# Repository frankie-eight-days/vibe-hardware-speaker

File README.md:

# Vibe hardware: a portable stereo Bluetooth speaker designed with LLM agents

A JBL Flip/Charge-class portable speaker, designed end to end with Claude Code agents and one human making the calls: requirements, part selection, circuit specs, KiCad schematic, simulations (acoustic BEM/FEM, SPICE, PDN), mechanical packaging and, next, PCB layout. The full story, including what went wrong, is in the write-up: [`docs/build/design_doc.pdf`](docs/build/design_doc.pdf). An interactive page explaining every simulation is in [`docs/viz/`](docs/viz/) (open `index.html`).

## The speaker

- **Stereo 2-way, bi-amped:** 2× Dayton ND65-8 woofers, 2× Peerless OT19NC00-04 tweeters (angled up 40°), 2× Dayton DMA58-PR passive radiators on the end caps. Bass to ~64 Hz (−3 dB), ~90 dB pink noise at 1 m on a desk.
- **Electronics:** ESP32-WROVER-E (Bluetooth A2DP + Wi-Fi EQ web UI), 2× TI TAS5805M class-D amps with DSP crossover/EQ/limiters, 18 V TPS61178 boost, BQ25792 buck-boost charger with USB-C PD (CH224Q), 2S Li-ion pack with on-board protection and balancing.
- **UI:** 1.28" round display, encoder, MEMS mic for placement-aware auto-EQ, power button.
- **Mechanics:** Ø95 × 210 mm capsule, five FDM-printed PETG parts, ~0.85 L net volume, ~12.8 h at moderate volume.
- **Manufacturing:** 4-layer main board assembled by JLCPCB from LCSC parts.

| | |
|---|---|
|  |  |
|  |  |

*Renders are placeholders until the Blender pass (after PCB layout and detailed CAD).*

## Status

| Stage | State |
|---|---|
| Requirements, research, part selection | Done |
| Circuit specs (power, signal, UI board) | v1.3 / v1.2 |
| Schematic | **v0.2**, release review passed with no blockers (`docs/review/`) |
| Simulations: acoustics, SPICE, PDN | Done (pre-layout) |
| Mechanical concept | Done (`mech/concept/`) |
| PCB layout | In progress |
| Thermal, post-layout PDN, EM hot-loop sims | After layout |
| Blender renders, build, REW measurements, firmware | Planned |

## Repository layout

| Path | Contents |
|---|---|
| `docs/requirements.md` | Single source of truth for product decisions |
| `docs/spec_*.md` | Pin-exact circuit specifications |
| `docs/eco_*.md`, `docs/review/` | Engineering changes and release reviews |
| `docs/process_log.md` | How the agents were orchestrated, and what went wrong |
| `docs/layout_principles.md` | Layout rules the PCB must meet |
| `docs/writeup/`, `docs/build/` | LaTeX write-up and its PDF |
| `docs/figures/` | All simulation figures (PDF + PNG) |
| `docs/renders/` | Blender renders (placeholders for now) |
| `research/` | Parts, drivers, firmware/tool research |
| `hw/mainboard/` | KiCad project; `hw/releases/` frozen snapshots; `hw/lib/` custom symbols/footprints |
| `mech/concept/` | Scripted FreeCAD packaging model, STEP, board envelopes |
| `sim/` | Acoustic, SPICE and PDN simulations (`run_all.sh` in each) |
| `kb/datasheets/` | Datasheet layout notes with page citations (vendor PDFs not included) |
| `tools/` | Helpers, e.g. the TAS5805M biquad encoder |

## Reproducing the simulations

```sh
python3 -m venv .venv && .venv/bin/pip install -r requirements-sim.txt
sim/acoustics/run_all.sh    # BEM runs take ~1 h on a laptop CPU
sim/spice/run_all.sh        # needs ngspice (brew install ngspice)
```

3D/CAD files and large simulation outputs (`*.step`, `*.stl`, `*.FCStd`, `*.npz`, raw waveforms) are stored with Git LFS: install it (`brew install git-lfs && git lfs install`) before cloning, or run `git lfs pull` afterwards.

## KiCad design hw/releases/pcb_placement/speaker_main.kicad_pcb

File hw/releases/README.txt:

v1 schematic snapshot, 2026-11-24, before the readability redraw.
ERC 0 violations. Exports in mainboard_v1/out/. Libraries frozen in releases/lib/.

v0.2 (release-ready for placement), 2026-11-24: redrawn, ECO-001 + ECO-002 applied, release review: no blockers, conditional on open should-fix items (docs/review/release_review.md, release_review_v0.2.md). Libraries frozen in releases/lib_v0.2/.

v0.3, 2026-11-25: ECO-004 (C605 47 uF Al-elec ESR-damped VBUS bulk, docs/eco_004.md). ERC 0 violations; netlist vs v0.2 differs only by C605 on VBUS/GND. Schematic-only snapshot (no .kicad_pcb: layout is live). Libraries: releases/lib_v0.2/.

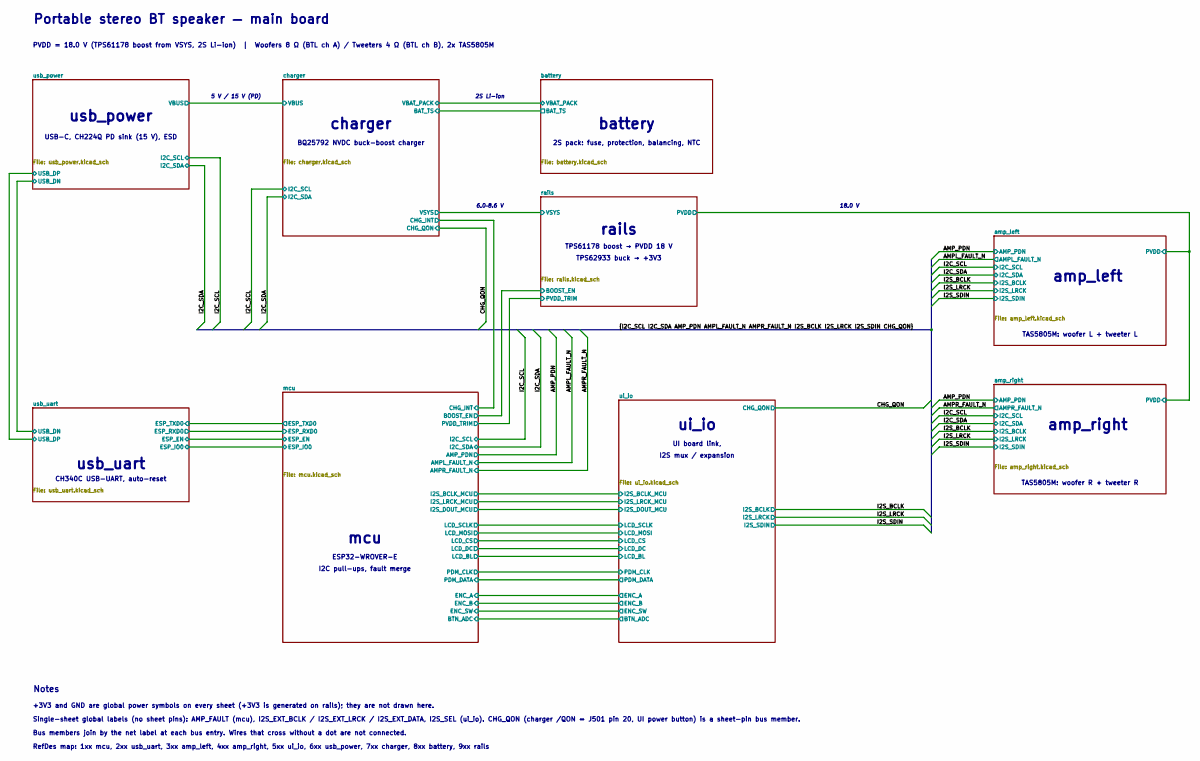
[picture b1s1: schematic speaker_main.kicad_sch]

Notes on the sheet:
Portable stereo BT speaker — main board
PVDD = 18.0 V (TPS61178 boost from VSYS, 2S Li-ion) | Woofers 8 Ω (BTL ch A) / Tweeters 4 Ω (BTL ch B), 2x TAS5805M
usb_power
USB-C, CH224Q PD sink (15 V), ESD
charger
BQ25792 NVDC buck-boost charger
battery
2S pack: fuse, protection, balancing, NTC
rails
TPS61178 boost → PVDD 18 V
TPS62933 buck → +3V3
usb_uart
CH340C USB-UART, auto-reset
mcu
ESP32-WROVER-E
I2C pull-ups, fault merge
ui_io
UI board link,
I2S mux / expansion
amp_left
TAS5805M: woofer L + tweeter L
amp_right
TAS5805M: woofer R + tweeter R
5 V / 15 V (PD)
2S Li-ion
6.0–8.6 V
18.0 V
Notes
+3V3 and GND are global power symbols on every sheet (+3V3 is generated on rails); they are not drawn here.
Bus members join by the net label at each bus entry. Wires that cross without a dot are not connected.
RefDes map: 1xx mcu, 2xx usb_uart, 3xx amp_left, 4xx amp_right, 5xx ui_io, 6xx usb_power, 7xx charger, 8xx battery, 9xx rails
Single-sheet global labels (no sheet pins): AMP_FAULT (mcu), I2S_EXT_BCLK / I2S_EXT_LRCK / I2S_EXT_DATA, I2S_SEL (ui_io). CHG_QON (charger /QON ↔ J501 pin 20, UI power button) is a sheet-pin bus member.

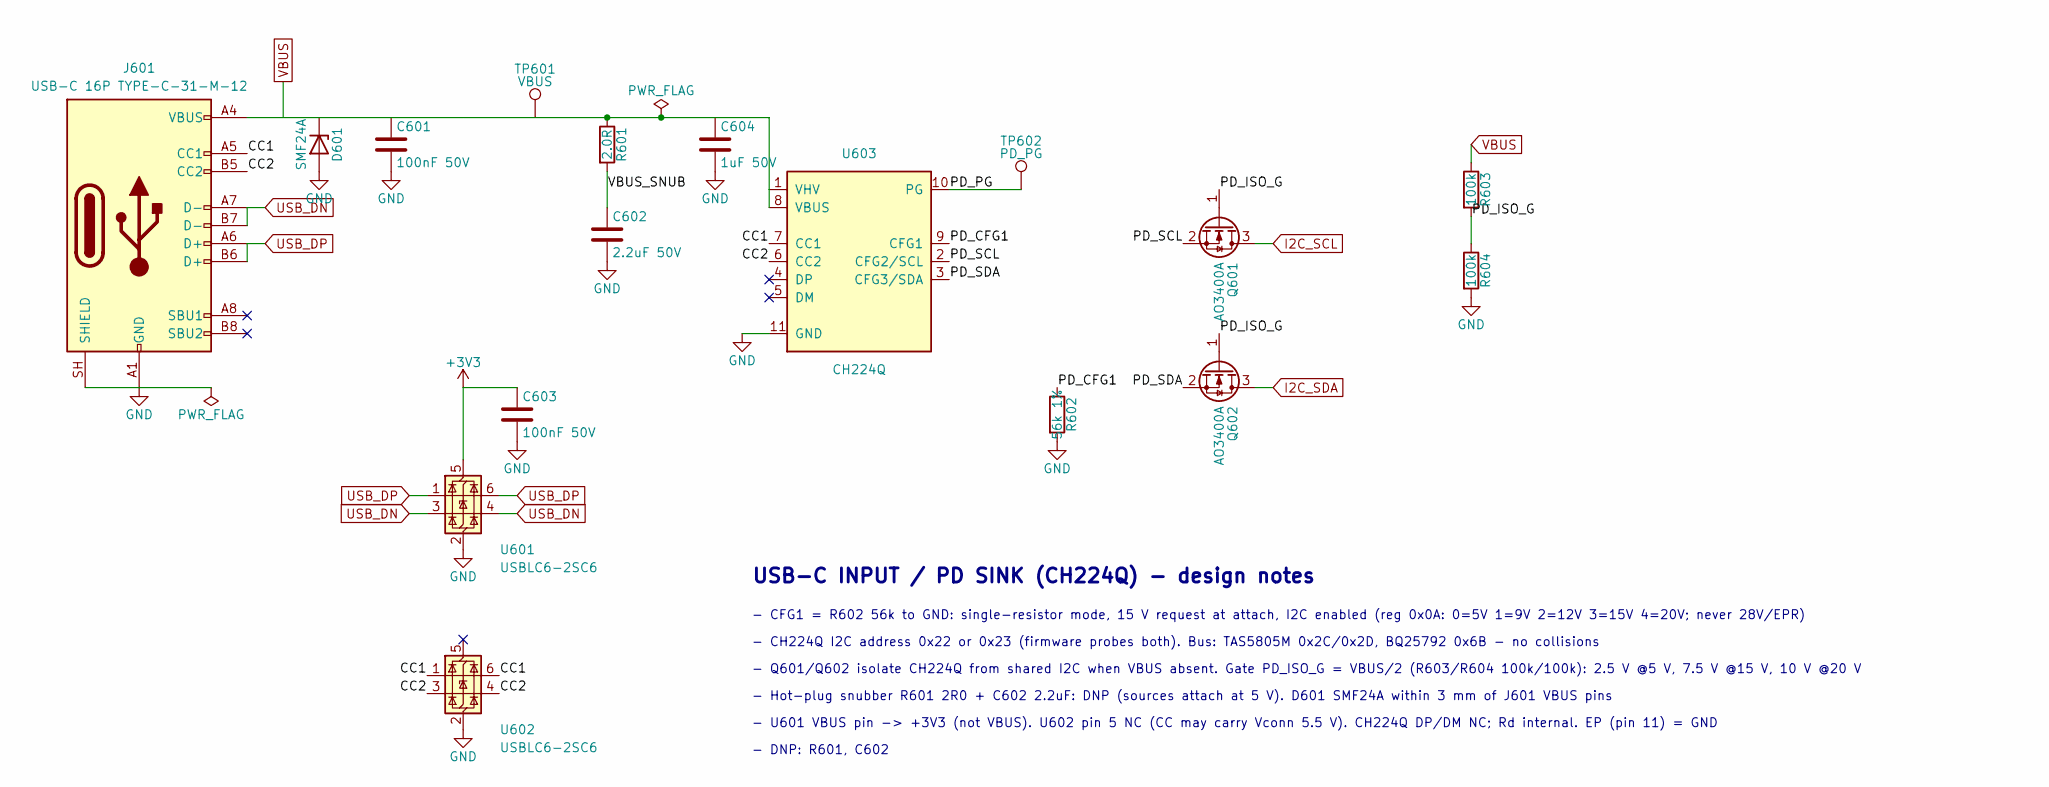
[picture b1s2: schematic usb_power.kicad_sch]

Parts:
C601, C603: 100nF 50V; C_0603_1608Metric; LCSC C14663
C602: 2.2uF 50V; C_0805_2012Metric; LCSC C377773
C604: 1uF 50V; C_0603_1608Metric; LCSC C15849
D601: SMF24A; D_SOD-123F; LCSC C123810
J601: USB-C 16P TYPE-C-31-M-12; USB_C_Receptacle_HRO_TYPE-C-31-M-12; LCSC C165948
Q601, Q602: AO3400A; SOT-23; LCSC C20917
R601: 2.0R; R_0805_2012Metric; LCSC C2930265
R602: 56k 1%; R_0603_1608Metric; LCSC C23206
R603, R604: 100k; R_0603_1608Metric; LCSC C25803
TP601: VBUS; TestPoint_Pad_D1.5mm
TP602: PD_PG; TestPoint_Pad_D1.5mm
U601, U602: USBLC6-2SC6; SOT-23-6; LCSC C2687116
U603: CH224Q; Texas_DSQ0010A_WSON-10-1EP_2x2mm_P0.4mm_EP0.9x1.5mm; LCSC C46061833

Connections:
+3V3: C603.1, U601.5 (VBUS); also elsewhere on the board
/I2C_SCL: Q601.3 (D); also elsewhere on the board
/I2C_SDA: Q602.3 (D); also elsewhere on the board
/usb_power/CC1: J601.A5 (CC1), U602.1 (I/O1), U602.6 (I/O1), U603.7 (CC1)
/usb_power/CC2: J601.B5 (CC2), U602.3 (I/O2), U602.4 (I/O2), U603.6 (CC2)
/usb_power/PD_CFG1: R602.1, U603.9 (CFG1)
/usb_power/PD_ISO_G: Q601.1 (G), Q602.1 (G), R603.2, R604.1
/usb_power/PD_PG: TP602.1 (1_1), U603.10 (PG)
/usb_power/PD_SCL: Q601.2 (S), U603.2 (CFG2/SCL)
/usb_power/PD_SDA: Q602.2 (S), U603.3 (CFG3/SDA)
/usb_power/USB_DN: J601.A7 (D-), J601.B7 (D-), U601.3 (I/O2), U601.4 (I/O2); also elsewhere on the board
/usb_power/USB_DP: J601.A6 (D+), J601.B6 (D+), U601.1 (I/O1), U601.6 (I/O1); also elsewhere on the board
/usb_power/VBUS_SNUB: C602.1, R601.2

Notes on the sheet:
USB-C INPUT / PD SINK (CH224Q) - design notes
- CFG1 = R602 56k to GND: single-resistor mode, 15 V request at attach, I2C enabled (reg 0x0A: 0=5V 1=9V 2=12V 3=15V 4=20V; never 28V/EPR)
- CH224Q I2C address 0x22 or 0x23 (firmware probes both). Bus: TAS5805M 0x2C/0x2D, BQ25792 0x6B - no collisions
- Q601/Q602 isolate CH224Q from shared I2C when VBUS absent. Gate PD_ISO_G = VBUS/2 (R603/R604 100k/100k): 2.5 V @5 V, 7.5 V @15 V, 10 V @20 V
- Hot-plug snubber R601 2R0 + C602 2.2uF: DNP (sources attach at 5 V). D601 SMF24A within 3 mm of J601 VBUS pins
- U601 VBUS pin -> +3V3 (not VBUS). U602 pin 5 NC (CC may carry Vconn 5.5 V). CH224Q DP/DM NC; Rd internal. EP (pin 11) = GND
- DNP: R601, C602

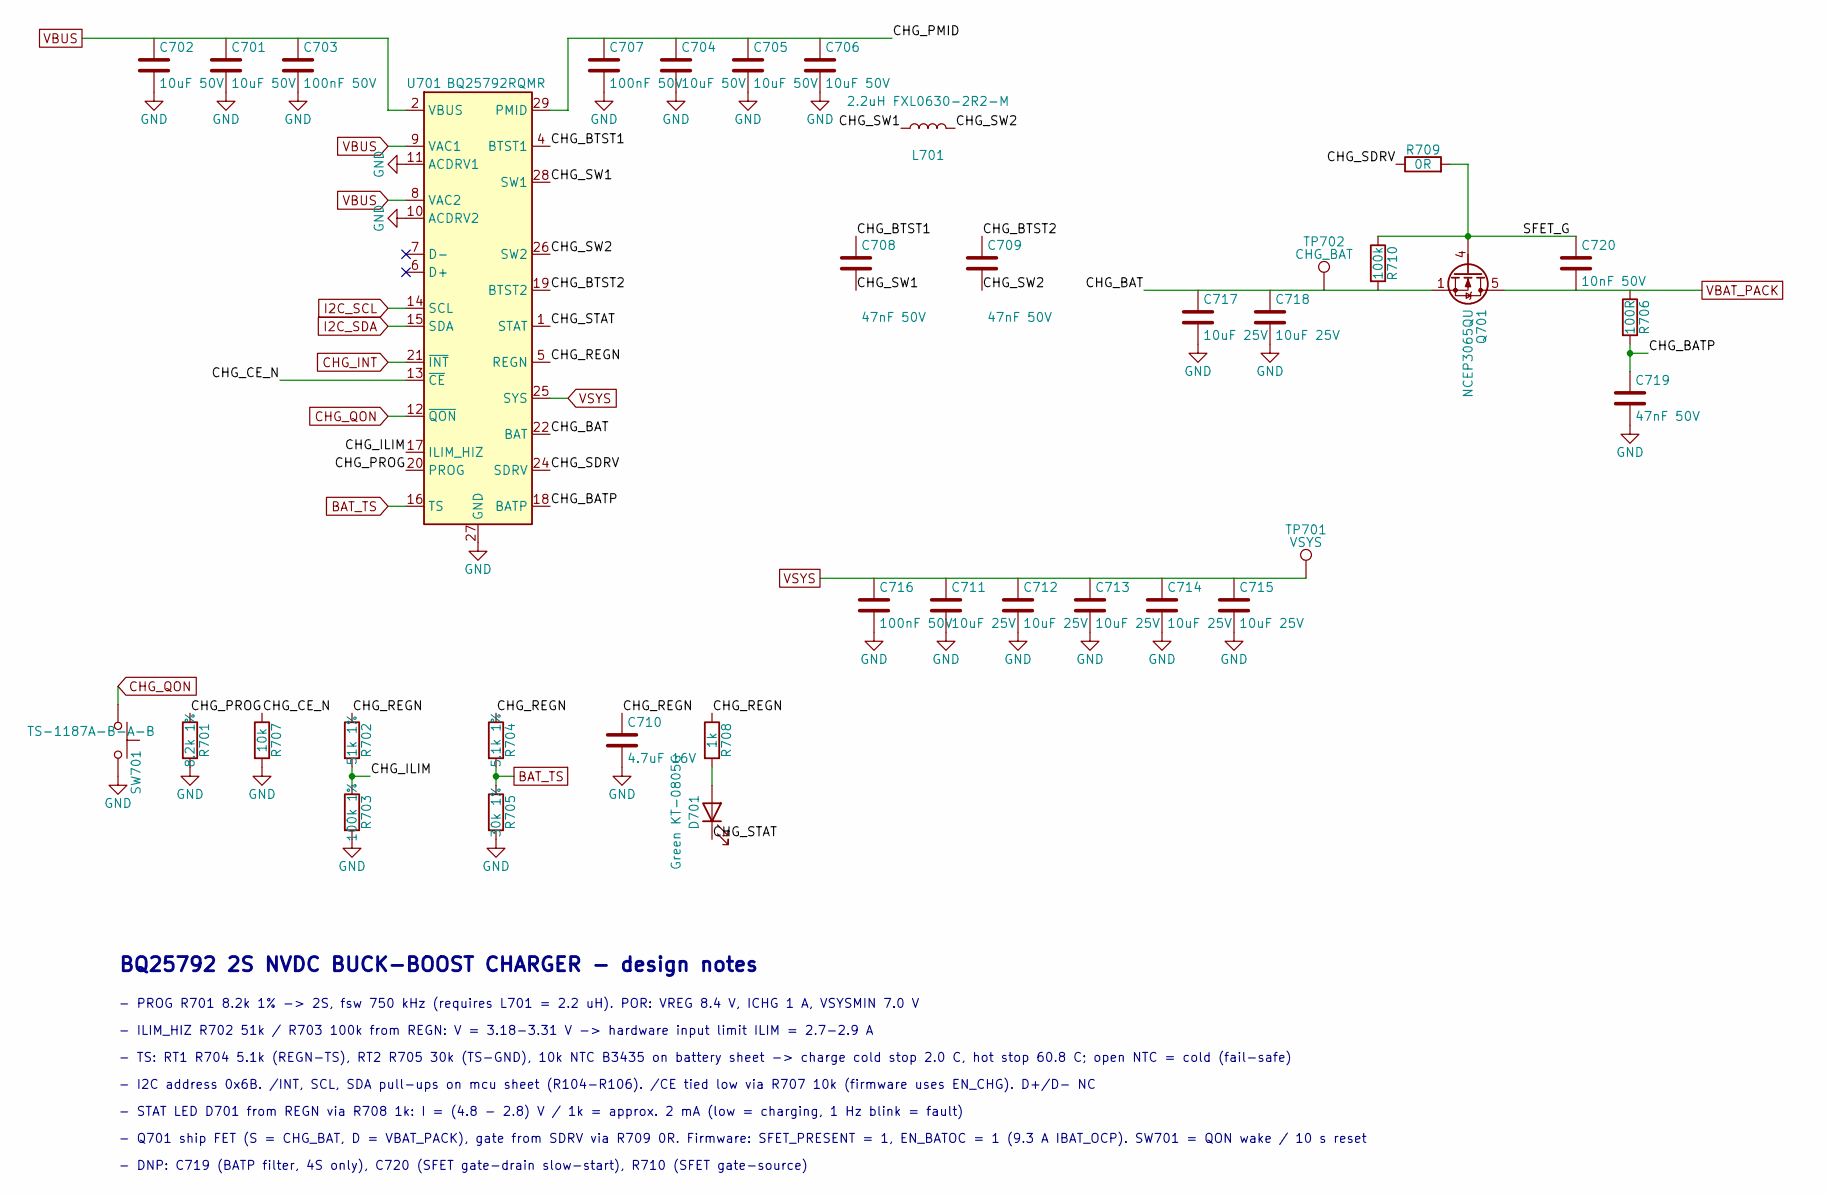
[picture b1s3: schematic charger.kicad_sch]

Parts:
C701, C702, C704, C705, C706: 10uF 50V; C_1206_3216Metric; LCSC C13585
C703, C707, C716: 100nF 50V; C_0603_1608Metric; LCSC C14663
C708, C709, C719: 47nF 50V; C_0603_1608Metric; LCSC C1622
C710: 4.7uF 16V; C_0603_1608Metric; LCSC C19666
C711, C712, C713, C714, C715, C717, C718: 10uF 25V; C_0805_2012Metric; LCSC C15850
C720: 10nF 50V; C_0603_1608Metric; LCSC C57112
D701: Green KT-0805G; LED_0805_2012Metric; LCSC C2297
L701: 2.2uH FXL0630-2R2-M; L_Changjiang_FXL0630; LCSC C167218
Q701: NCEP3065QU; VSON-8_3.3x3.3mm_P0.65mm_NexFET; LCSC C502964
R701: 8.2k 1%; R_0603_1608Metric; LCSC C25981
R702: 51k 1%; R_0603_1608Metric; LCSC C23196
R703: 100k 1%; R_0603_1608Metric; LCSC C25803
R704: 5.1k 1%; R_0603_1608Metric; LCSC C23186
R705: 30k 1%; R_0603_1608Metric; LCSC C22984
R706: 100R; R_0603_1608Metric; LCSC C22775
R707: 10k; R_0603_1608Metric; LCSC C25804
R708: 1k; R_0603_1608Metric; LCSC C21190
R709: 0R; R_0603_1608Metric; LCSC C21189
R710: 100k; R_0603_1608Metric; LCSC C25803
SW701: TS-1187A-B-A-B; SW_Push_1P1T_XKB_TS-1187A; LCSC C318884
TP701: VSYS; TestPoint_Pad_D1.5mm
TP702: CHG_BAT; TestPoint_Pad_D1.5mm
U701: BQ25792RQMR; Texas_RQM0029A_VQFN-29_4x4mm_P0.4mm; LCSC C2862876

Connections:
/CHG_QON: SW701.1, U701.12 (~QON); also elsewhere on the board
/I2C_SCL: U701.14 (SCL); also elsewhere on the board
/I2C_SDA: U701.15 (SDA); also elsewhere on the board
/battery/BAT_TS: R704.2, R705.1, U701.16 (TS); also elsewhere on the board
/battery/VBAT_PACK: C720.2, Q701.5 (D), R706.1; also elsewhere on the board
/charger/CHG_BAT: C717.1, C718.1, Q701.1 (S), Q701.2 (S), Q701.3 (S), R710.2, TP702.1 (1_1), U701.22 (BAT), U701.23 (BAT); also elsewhere on the board
/charger/CHG_BATP: C719.1, R706.2, U701.18 (BATP)
/charger/CHG_BTST1: C708.1, U701.4 (BTST1)
/charger/CHG_BTST2: C709.1, U701.19 (BTST2)
/charger/CHG_CE_N: R707.1, U701.13 (~CE)
/charger/CHG_ILIM: R702.2, R703.1, U701.17 (ILIM_HIZ)
/charger/CHG_INT: U701.21 (~INT); also elsewhere on the board
/charger/CHG_PMID: C704.1, C705.1, C706.1, C707.1, U701.29 (PMID)
/charger/CHG_PROG: R701.1, U701.20 (PROG)
/charger/CHG_REGN: C710.1, R702.1, R704.1, R708.1, U701.5 (REGN)
/charger/CHG_SDRV: R709.1, U701.24 (SDRV)
/charger/CHG_STAT: D701.1 (K), U701.1 (STAT)
/charger/CHG_SW1: C708.2, L701.1, U701.28 (SW1)
/charger/CHG_SW2: C709.2, L701.2, U701.26 (SW2)
/charger/SFET_G: C720.1, Q701.4 (G), R709.2, R710.1; also elsewhere on the board
/charger/VSYS: C711.1, C712.1, C713.1, C714.1, C715.1, C716.1, TP701.1 (1_1), U701.25 (SYS); also elsewhere on the board
unnamed: D701.2 (A), R708.2

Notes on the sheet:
BQ25792 2S NVDC BUCK-BOOST CHARGER - design notes
- PROG R701 8.2k 1% -> 2S, fsw 750 kHz (requires L701 = 2.2 uH). POR: VREG 8.4 V, ICHG 1 A, VSYSMIN 7.0 V
- ILIM_HIZ R702 51k / R703 100k from REGN: V = 3.18-3.31 V -> hardware input limit ILIM = 2.7-2.9 A
- TS: RT1 R704 5.1k (REGN-TS), RT2 R705 30k (TS-GND), 10k NTC B3435 on battery sheet -> charge cold stop 2.0 C, hot stop 60.8 C; open NTC = cold (fail-safe)
- I2C address 0x6B. /INT, SCL, SDA pull-ups on mcu sheet (R104-R106). /CE tied low via R707 10k (firmware uses EN_CHG). D+/D- NC
- STAT LED D701 from REGN via R708 1k: I = (4.8 - 2.8) V / 1k = approx. 2 mA (low = charging, 1 Hz blink = fault)
- Q701 ship FET (S = CHG_BAT, D = VBAT_PACK), gate from SDRV via R709 0R. Firmware: SFET_PRESENT = 1, EN_BATOC = 1 (9.3 A IBAT_OCP). SW701 = QON wake / 10 s reset
- DNP: C719 (BATP filter, 4S only), C720 (SFET gate-drain slow-start), R710 (SFET gate-source)

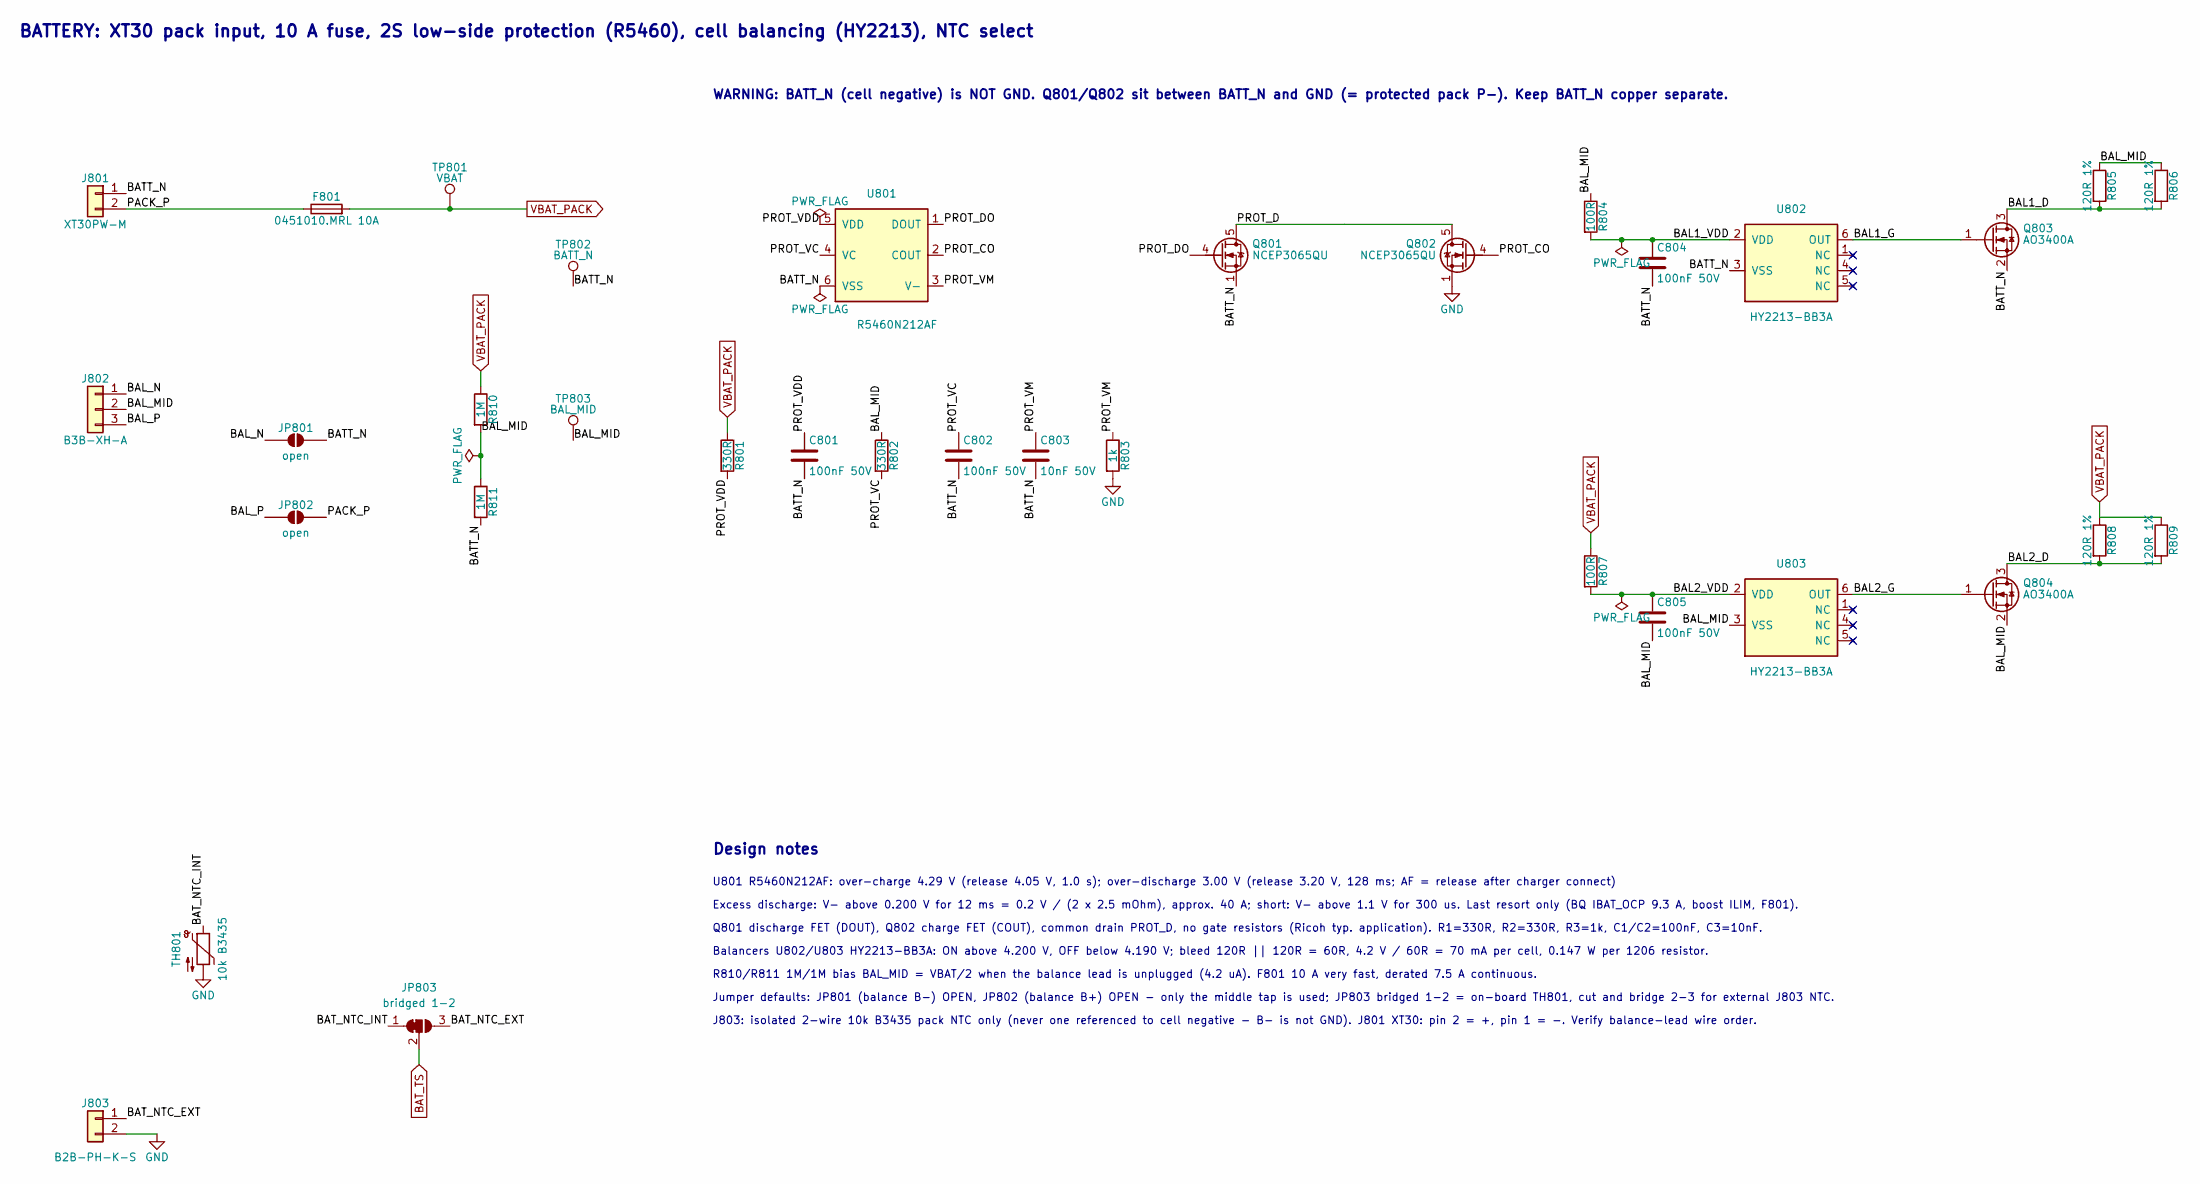
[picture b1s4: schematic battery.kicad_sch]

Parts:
C801, C802, C804, C805: 100nF 50V; C_0603_1608Metric; LCSC C14663
C803: 10nF 50V; C_0603_1608Metric; LCSC C57112
F801: 0451010.MRL 10A; Fuse_2410_6125Metric; LCSC C44479
J801: XT30PW-M; AMASS_XT30PW-M_1x02_P2.50mm_Horizontal; LCSC C431092
J802: B3B-XH-A; JST_XH_B3B-XH-A_1x03_P2.50mm_Vertical; LCSC C144394
J803: B2B-PH-K-S; JST_PH_B2B-PH-K_1x02_P2.00mm_Vertical; LCSC C131337
JP801, JP802: open; SolderJumper-2_P1.3mm_Open_RoundedPad1.0x1.5mm
JP803: bridged 1-2; SolderJumper-3_P1.3mm_Bridged12_RoundedPad1.0x1.5mm
Q801, Q802: NCEP3065QU; VSON-8_3.3x3.3mm_P0.65mm_NexFET; LCSC C502964
Q803, Q804: AO3400A; SOT-23; LCSC C20917
R801, R802: 330R; R_0603_1608Metric; LCSC C23138
R803: 1k; R_0603_1608Metric; LCSC C21190
R804, R807: 100R; R_0603_1608Metric; LCSC C22775
R805, R806, R808, R809: 120R 1%; R_1206_3216Metric; LCSC C17909
R810, R811: 1M; R_0603_1608Metric; LCSC C22935
TH801: 10k B3435; R_0603_1608Metric; LCSC C2889048
TP801: VBAT; TestPoint_Pad_D1.5mm
TP802: BATT_N; TestPoint_Pad_D1.5mm
TP803: BAL_MID; TestPoint_Pad_D1.5mm
U801: R5460N212AF; SOT-23-6; LCSC C259717
U802, U803: HY2213-BB3A; SOT-23-6; LCSC C113632

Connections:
/battery/BAL1_D: Q803.3 (D), R805.2, R806.2
/battery/BAL1_G: Q803.1 (G), U802.6 (OUT)
/battery/BAL2_D: Q804.3 (D), R808.2, R809.2
/battery/BAL2_G: Q804.1 (G), U803.6 (OUT)
/battery/BAL_N: J802.1, JP801.1 (A)
/battery/BAL_P: J802.3, JP802.1 (A)
/battery/BAT_TS: JP803.2 (C); also elsewhere on the board
/battery/PACK_P: F801.1, J801.2, JP802.2 (B)
/battery/PROT_CO: Q802.4 (G), U801.2 (COUT)
/battery/PROT_D: Q801.5 (D), Q802.5 (D)
/battery/PROT_DO: Q801.4 (G), U801.1 (DOUT)
/battery/PROT_VC: C802.1, R802.2, U801.4 (VC)
/battery/PROT_VM: C803.1, R803.1, U801.3 (V-)
/battery/VBAT_PACK: F801.2, R801.1, R807.1, R808.1, R809.1, R810.1, TP801.1 (1_1); also elsewhere on the board

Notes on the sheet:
BATTERY: XT30 pack input, 10 A fuse, 2S low-side protection (R5460), cell balancing (HY2213), NTC select
WARNING: BATT_N (cell negative) is NOT GND. Q801/Q802 sit between BATT_N and GND (= protected pack P-). Keep BATT_N copper separate.
Design notes
U801 R5460N212AF: over-charge 4.29 V (release 4.05 V, 1.0 s); over-discharge 3.00 V (release 3.20 V, 128 ms; AF = release after charger connect)
Q801 discharge FET (DOUT), Q802 charge FET (COUT), common drain PROT_D, no gate resistors (Ricoh typ. application). R1=330R, R2=330R, R3=1k, C1/C2=100nF, C3=10nF.
R810/R811 1M/1M bias BAL_MID = VBAT/2 when the balance lead is unplugged (4.2 uA). F801 10 A very fast, derated 7.5 A continuous.
Jumper defaults: JP801 (balance B-) OPEN, JP802 (balance B+) OPEN - only the middle tap is used; JP803 bridged 1-2 = on-board TH801, cut and bridge 2-3 for external J803 NTC.
J803: isolated 2-wire 10k B3435 pack NTC only (never one referenced to cell negative - B- is not GND). J801 XT30: pin 2 = +, pin 1 = -. Verify balance-lead wire order.
Excess discharge: V- above 0.200 V for 12 ms = 0.2 V / (2 x 2.5 mOhm), approx. 40 A; short: V- above 1.1 V for 300 us. Last resort only (BQ IBAT_OCP 9.3 A, boost ILIM, F801).
Balancers U802/U803 HY2213-BB3A: ON above 4.200 V, OFF below 4.190 V; bleed 120R || 120R = 60R, 4.2 V / 60R = 70 mA per cell, 0.147 W per 1206 resistor.

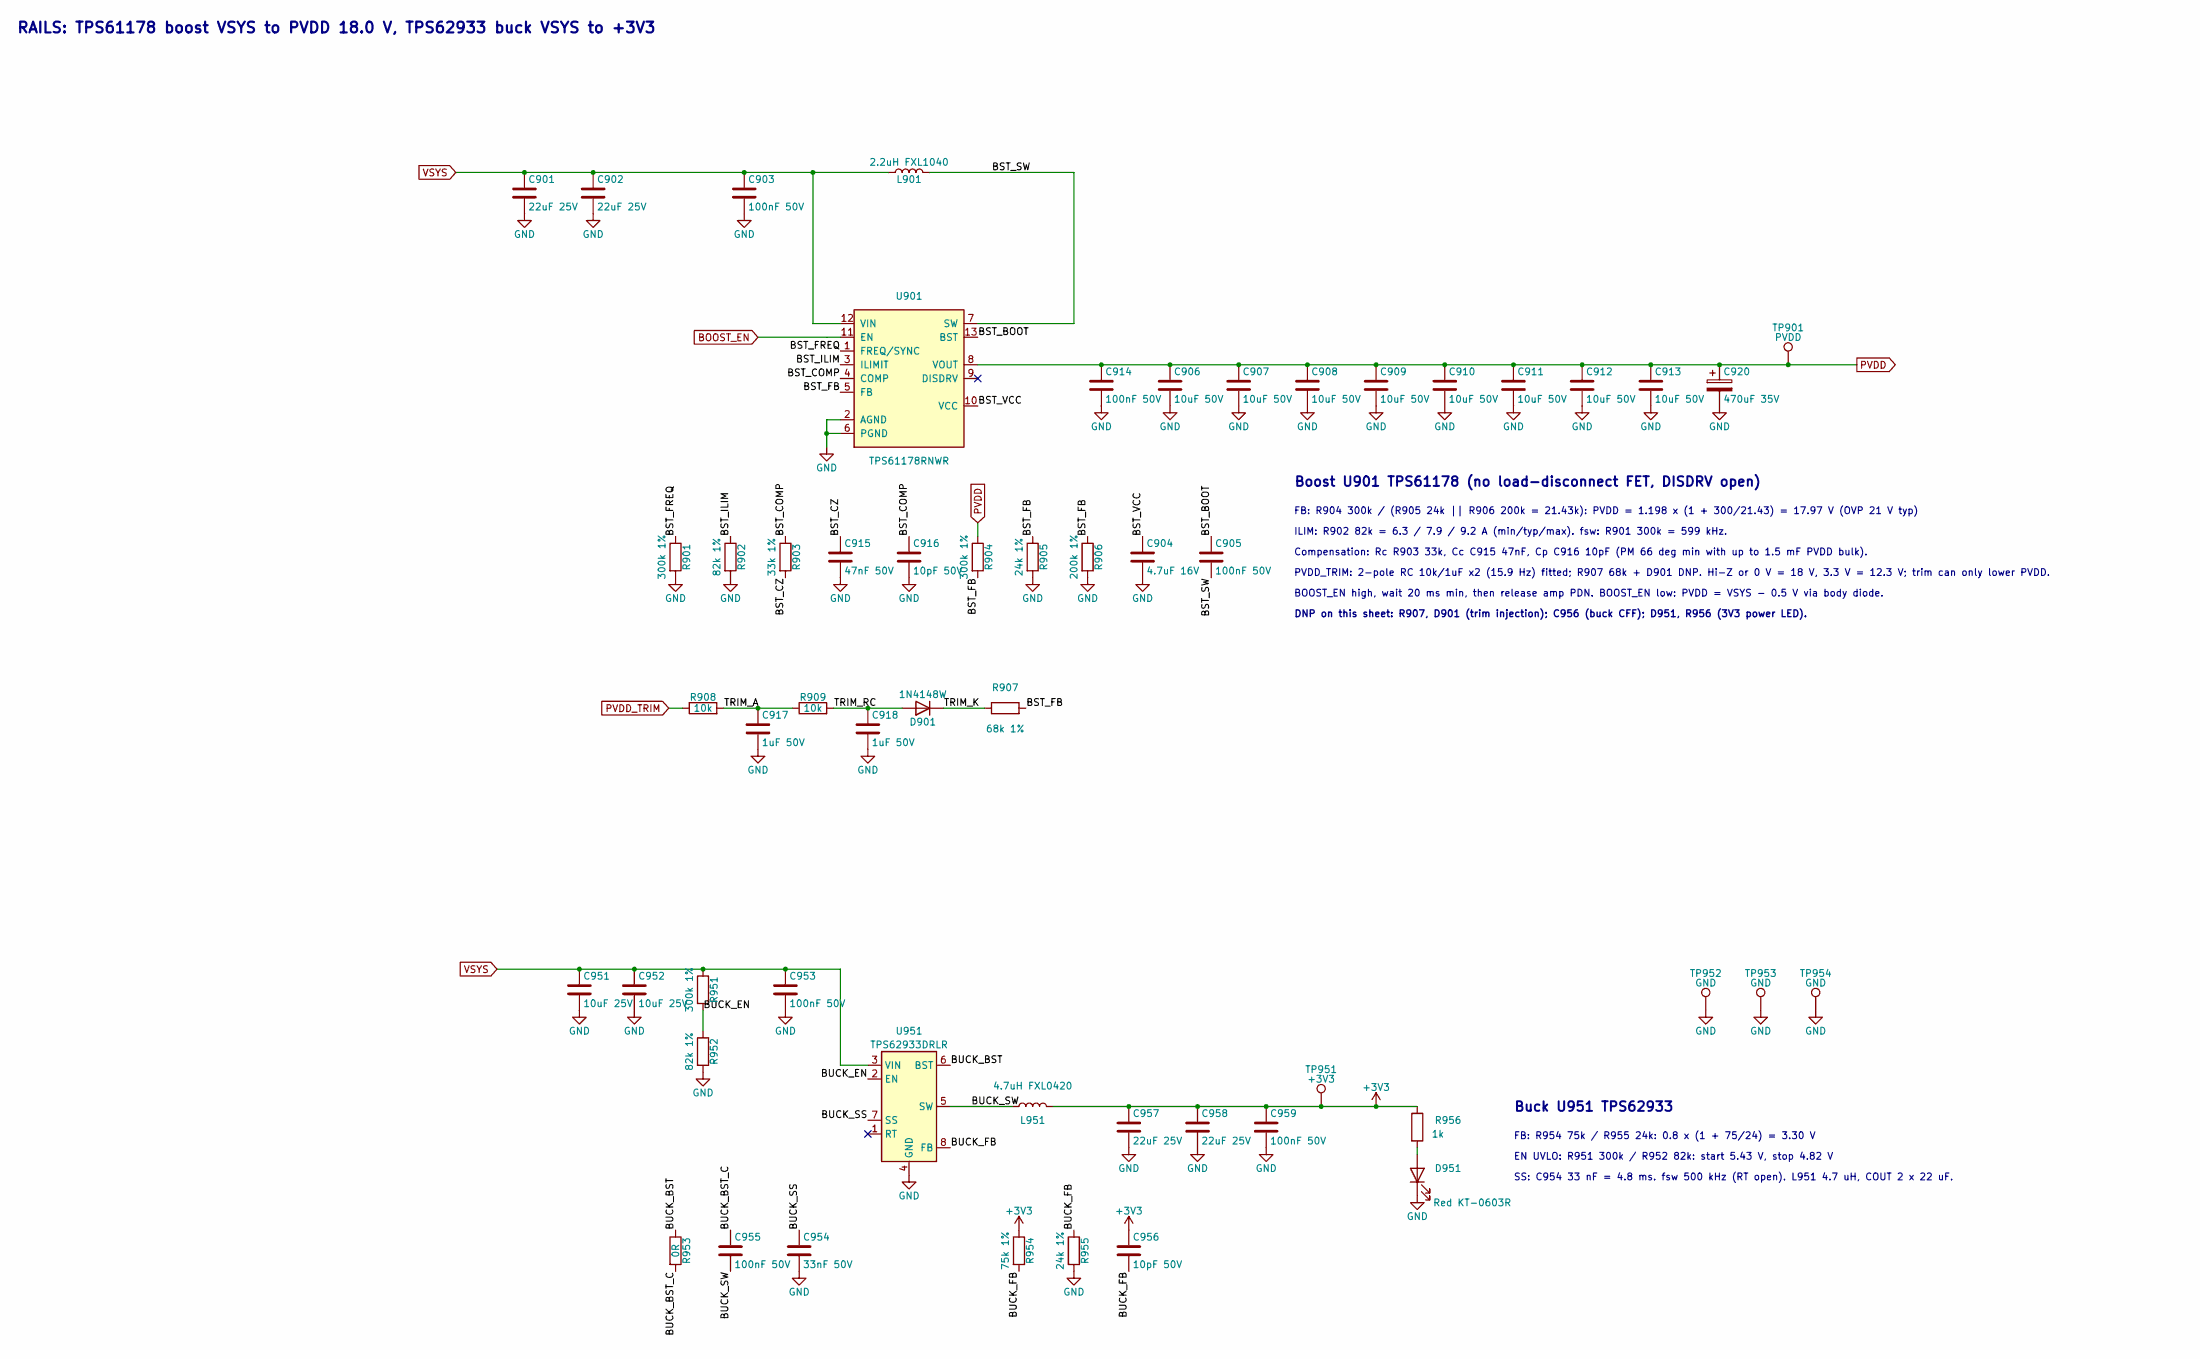
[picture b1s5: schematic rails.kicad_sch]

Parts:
C901, C902, C957, C958: 22uF 25V; C_1206_3216Metric; LCSC C12891
C903, C905, C914, C953, C955, C959: 100nF 50V; C_0603_1608Metric; LCSC C14663
C904: 4.7uF 16V; C_0603_1608Metric; LCSC C19666
C906, C907, C908, C909, C910, C911, C912, C913: 10uF 50V; C_1206_3216Metric; LCSC C13585
C915: 47nF 50V; C_0603_1608Metric; LCSC C1622
C916, C956: 10pF 50V; C_0603_1608Metric; LCSC C1634
C917, C918: 1uF 50V; C_0603_1608Metric; LCSC C15849
C920: 470uF 35V; CP_Elec_10x10.5; LCSC C2836436
C951, C952: 10uF 25V; C_0805_2012Metric; LCSC C15850
C954: 33nF 50V; C_0603_1608Metric; LCSC C21117
D901: 1N4148W; D_SOD-123; LCSC C81598
D951: Red KT-0603R; LED_0603_1608Metric; LCSC C2286
L901: 2.2uH FXL1040; L_Changjiang_FXL1040; LCSC C167228
L951: 4.7uH FXL0420; L_Changjiang_FXL0420; LCSC C167208
R901, R904, R951: 300k 1%; R_0603_1608Metric; LCSC C23024
R902, R952: 82k 1%; R_0603_1608Metric; LCSC C23254
R903: 33k 1%; R_0603_1608Metric; LCSC C4216
R905, R955: 24k 1%; R_0603_1608Metric; LCSC C23352
R906: 200k 1%; R_0603_1608Metric; LCSC C25811
R907: 68k 1%; R_0603_1608Metric; LCSC C23231
R908, R909: 10k; R_0603_1608Metric; LCSC C25804
R953: 0R; R_0603_1608Metric; LCSC C21189
R954: 75k 1%; R_0603_1608Metric; LCSC C23242
R956: 1k; R_0603_1608Metric; LCSC C21190
TP901: PVDD; TestPoint_Pad_D2.0mm
TP951: +3V3; TestPoint_Pad_D1.5mm
TP952, TP953, TP954: GND; TestPoint_Pad_D2.0mm
U901: TPS61178RNWR; Texas_RNW0013A_VQFN-HR-13_3x3.5mm_P0.5mm; LCSC C127918
U951: TPS62933DRLR; SOT-583-8; LCSC C3200405

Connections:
+3V3: C956.1, C957.1, C958.1, C959.1, L951.2, R954.1, R956.1, TP951.1 (1_1); also elsewhere on the board
/amp_left/PVDD: C906.1, C907.1, C908.1, C909.1, C910.1, C911.1, C912.1, C913.1, C914.1, C920.1, R904.1, TP901.1 (1_1), U901.8 (VOUT); also elsewhere on the board
/charger/VSYS: C901.1, C902.1, C903.1, C951.1, C952.1, C953.1, L901.1, R951.1, U901.12 (VIN), U951.3 (VIN); also elsewhere on the board
/mcu/BOOST_EN: U901.11 (EN); also elsewhere on the board
/mcu/PVDD_TRIM: R908.1; also elsewhere on the board
/rails/BST_BOOT: C905.1, U901.13 (BST)
/rails/BST_COMP: C916.1, R903.1, U901.4 (COMP)
/rails/BST_CZ: C915.1, R903.2
/rails/BST_FB: R904.2, R905.1, R906.1, R907.2, U901.5 (FB)
/rails/BST_FREQ: R901.1, U901.1 (FREQ/SYNC)
/rails/BST_ILIM: R902.1, U901.3 (ILIMIT)
/rails/BST_SW: C905.2, L901.2, U901.7 (SW)
/rails/BST_VCC: C904.1, U901.10 (VCC)
/rails/BUCK_BST: R953.1, U951.6 (BST)
/rails/BUCK_BST_C: C955.1, R953.2
/rails/BUCK_EN: R951.2, R952.1, U951.2 (EN)
/rails/BUCK_FB: C956.2, R954.2, R955.1, U951.8 (FB)
/rails/BUCK_SS: C954.1, U951.7 (SS)
/rails/BUCK_SW: C955.2, L951.1, U951.5 (SW)
/rails/TRIM_A: C917.1, R908.2, R909.1
/rails/TRIM_K: D901.1 (K), R907.1
/rails/TRIM_RC: C918.1, D901.2 (A), R909.2
unnamed: D951.2 (A), R956.2

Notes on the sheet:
RAILS: TPS61178 boost VSYS to PVDD 18.0 V, TPS62933 buck VSYS to +3V3
Boost U901 TPS61178 (no load-disconnect FET, DISDRV open)
FB: R904 300k / (R905 24k || R906 200k = 21.43k): PVDD = 1.198 x (1 + 300/21.43) = 17.97 V (OVP 21 V typ)
ILIM: R902 82k = 6.3 / 7.9 / 9.2 A (min/typ/max). fsw: R901 300k = 599 kHz.
Compensation: Rc R903 33k, Cc C915 47nF, Cp C916 10pF (PM 66 deg min with up to 1.5 mF PVDD bulk).
PVDD_TRIM: 2-pole RC 10k/1uF x2 (15.9 Hz) fitted; R907 68k + D901 DNP. Hi-Z or 0 V = 18 V, 3.3 V = 12.3 V; trim can only lower PVDD.
BOOST_EN high, wait 20 ms min, then release amp PDN. BOOST_EN low: PVDD = VSYS - 0.5 V via body diode.
DNP on this sheet: R907, D901 (trim injection); C956 (buck CFF); D951, R956 (3V3 power LED).
Buck U951 TPS62933
FB: R954 75k / R955 24k: 0.8 x (1 + 75/24) = 3.30 V
EN UVLO: R951 300k / R952 82k: start 5.43 V, stop 4.82 V
SS: C954 33 nF = 4.8 ms. fsw 500 kHz (RT open). L951 4.7 uH, COUT 2 x 22 uF.
